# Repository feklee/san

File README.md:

Introduction
============

*Knowing yourself is the beginning of all wisdom* ― Aristotle

SAN (Self Aware Network) is an experiment about the [future of
architecture][1]. The network understands its own topology, a first
step towards being able to dynamically adapt to its environment.

SAN is an intermediate step: [Manifesto][6]

Getting started
===============

 1. Build nodes, edges, and the root node.

 2. Program the root node and the nodes.

 3. If using the USB root node, connect that to your computer, then run the web
    app.
    
    If using the WiFi root node, simply connect to it with a web browser.
    
 4. Build a structure.

There may be [apps][5] built on top of the system.

Acknowledgments
===============

  * [Cong Nguyen][2] for helping with PCB design

  * [David Mickisch][3] for mathematical advise and for writing the
    experimental [San-Optimizer][4]
    
  * Herbert Poetzl for advice on electronics and for the suggestion to
    use optical communication between nodes
  
  * Loay Yari for helping with PCB design and manufacturing
    
  * [Pietro Mincuzzi][7] for the o-ring trick
  
  * Kliment for advice on electronics, optics, and the ESP32

License
=======

Except where noted otherwise, files are licensed under the WTFPL.

Copyright © 2018–2020 [Felix E. Klee](felix.klee@inka.de)

This work is free. You can redistribute it and/or modify it under the terms of
the Do What The Fuck You Want To Public License, Version 2, as published by Sam
Hocevar. See the COPYING file for more details.

[1]: https://feklee.github.io/san/notes/128a47a0-23ea-11e9-a8da-000c296198cf/
[2]: https://github.com/rampadc
[3]: https://github.com/davidblitz
[4]: https://github.com/davidblitz/san-optimizer
[5]: https://feklee.github.io/san/notes/f8d89da9-c285-4b5a-921b-7af3444b9229/
[6]: https://feklee.github.io/san/notes/0411b82f-268f-46b2-9563-efaf14a68a41/
[7]: https://pietro.mincuzzi.asia

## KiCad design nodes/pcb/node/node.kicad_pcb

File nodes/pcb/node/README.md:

This repo has been merged into the [SAN][1] repo as a [Git subtree][2].

To update this repo from within the SAN repo, [run][3] from the toplevel of the
SAN working tree:

    git subtree push --prefix=$PATH_OF_TREE $THIS_REPO master

Replace `$PATH_OF_TREE` and `$THIS_REPO` appropriately.

[1]: https://github.com/feklee/san
[2]: https://git-scm.com/book/en/v1/Git-Tools-Subtree-Merging
[3]: https://stackoverflow.com/a/55400804/282729

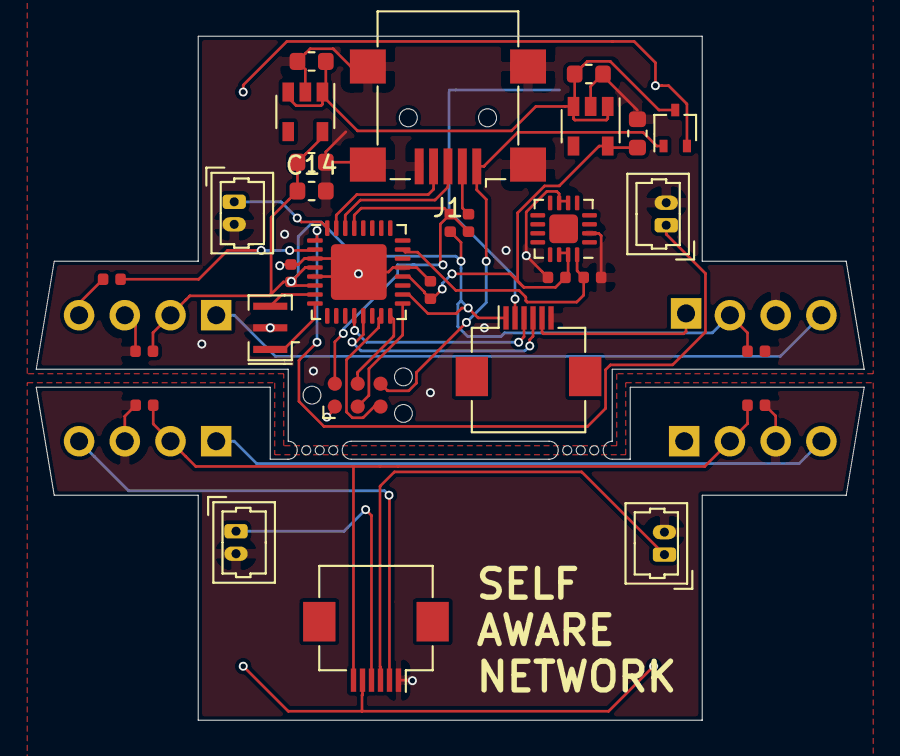
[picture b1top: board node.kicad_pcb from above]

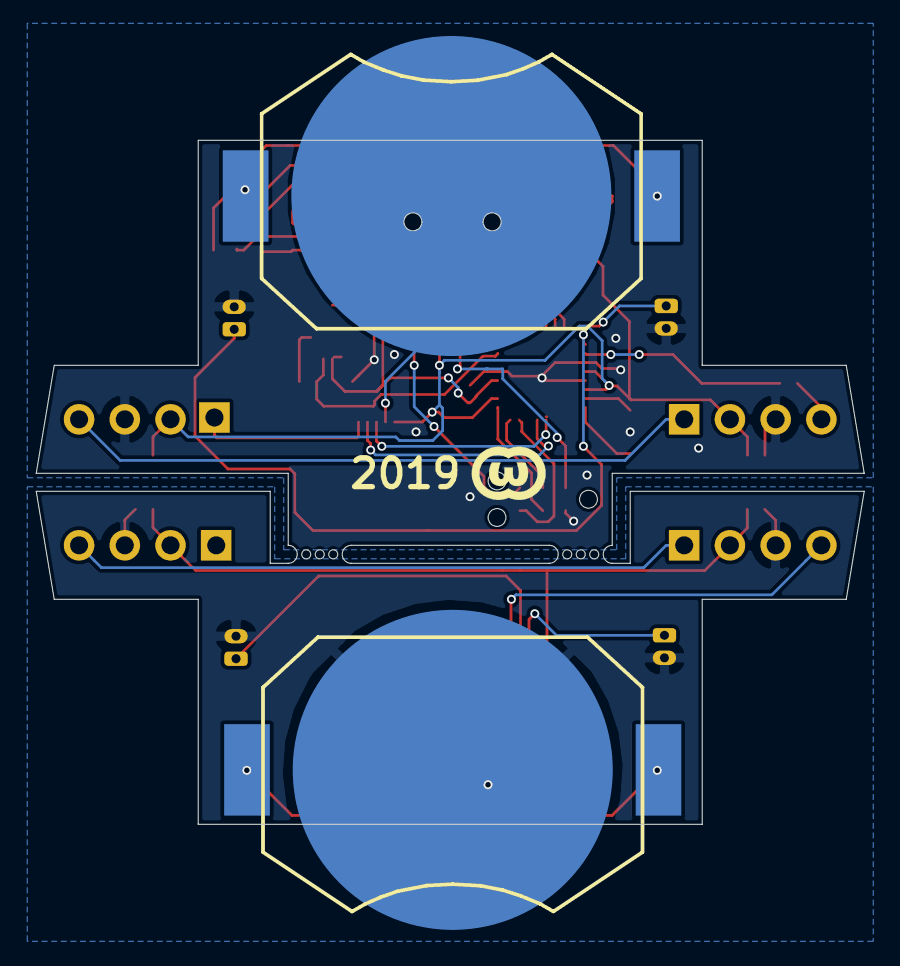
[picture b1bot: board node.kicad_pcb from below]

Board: 2 copper layers, 46.0 x 38.0 mm, 38 parts (2 on the bottom side), 32 nets.

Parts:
BT1, BT2: CR2032; BK-912
C1, C2, C3, C4, C14: 1u; C_0603_1608Metric
C5, C6, C7, C8, C9, C10, C11, C12, C13: 0.1u; C_0402_1005Metric
D1: BAT54CW; SOT-323_SC-70
D2, D3, D4, D5: WS2812D-F5
J1: USB_B_Mini; USB_Mini-B
J2: TC2030_NL; Tag-Connect_TC2030-IDC-NL_2x03_P1.27mm_Vertical
J3, J6: FFC-0.5MM-6POS; Hirose_FH12-6S-0.5SH_1x06-1MP_P0.50mm_Horizontal
J4: Port_1; Molex_PicoBlade_53047-0210_1x02_P1.25mm_Vertical
J5: Port_2; Molex_PicoBlade_53047-0210_1x02_P1.25mm_Vertical
J7: Port_3; Molex_PicoBlade_53047-0210_1x02_P1.25mm_Vertical
J8: Port_4; Molex_PicoBlade_53047-0210_1x02_P1.25mm_Vertical
R1: 10K; R_0402_1005Metric
R2: 470R; R_0402_1005Metric
U1: PMIC-LDO-XC6204B332MR_SOT23-5; SOT-23-5
U2: LP2985-5.0; SOT-23-5
U3: ATmega328P-MU; QFN-32-1EP_5x5mm_P0.5mm_EP3.1x3.1mm
U4: ADXL337; LFCSP-16-1EP_3x3mm_P0.5mm_EP1.6x1.6mm
Y1: 16MHz; Resonator_SMD_muRata_CSTxExxV-3Pin_3.0x1.1mm
mouse-bite: VAL**; mouse-bite
mouse-bite#2: VAL**; mouse-bite

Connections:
+3V3: C4.1, C5.1, C8.1, U1.5, U3.20, U4.14, U4.15
+5V: C3.2, C6.1, C9.1, C11.1, C14.1, D2.2, D3.2, J3.1, R1.1, U2.5, U3.4, U3.6, U3.18
+5VB: C12.1, C13.1, D4.2, D5.2, J6.6
/Bottom hemisphere/BATT-BOT: BT2.1, J6.5
/Bottom hemisphere/BNC-3: J6.4, J7.1
/Bottom hemisphere/BNC-4: J6.3, J8.1
/Bottom hemisphere/DOUT: D4.4, J6.2
/Top Hemisphere/+5V_EXT: D1.1, J1.1, J2.6
/Top Hemisphere/BATT: BT1.1, D1.2
/Top Hemisphere/BATT-BOT: BT1.2, J3.2
/Top Hemisphere/BNC-1: J4.1, U3.32
/Top Hemisphere/BNC-2: J5.1, U3.1
/Top Hemisphere/BNC-3: J3.3, U3.12
/Top Hemisphere/BNC-4: J3.4, U3.13
/Top Hemisphere/DIN-TOP: D2.4, R2.1
/Top Hemisphere/DOUT: D3.1, J3.5
/Top Hemisphere/DTR: C7.1, J1.2
/Top Hemisphere/MISO: J2.4, U3.16
/Top Hemisphere/MOSI: J2.5, U3.15
/Top Hemisphere/RXI: J1.3, U3.30
/Top Hemisphere/SCK: J2.3, U3.17
/Top Hemisphere/TXO: J1.4, U3.31
/Top Hemisphere/VIN: C1.1, C2.1, D1.3, U1.1, U1.3, U2.1, U2.3
/Top Hemisphere/Z-ACCEL: C10.1, U3.23, U4.16
/Top Hemisphere/~RST: C7.2, J2.2, R1.2, U3.29
GND: C1.2, C2.2, C3.1, C4.2, C5.2, C6.2, C8.2, C9.2, C10.2, C11.2, C14.2, D2.3, D3.3, J1.5, J1.6, J2.1, J3.6, J4.2, J5.2, U1.2, U2.2, U3.3, U3.5, U3.21, U3.33, U4.2, U4.6, U4.7, Y1.2
GNDB: BT2.2, C12.2, C13.2, D4.3, D5.3, J6.1, J7.2, J8.2
unnamed: D2.1, D3.4
unnamed: D4.1, D5.4
unnamed: R2.2, U3.2
unnamed: U3.7, Y1.3
unnamed: U3.8, Y1.1

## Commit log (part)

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2019-06-13 Mention mood
2019-06-13 Add app ideas
2019-06-13 Allow offsetting curve out of the way
2019-06-13 Turn cursor to pointer over buttons
2019-06-15 Prevent accidental overscroll
2019-06-15 Change spectrum analyzer stroke
2019-06-15 Make sawtooth button label graphical
2019-06-15 Switch from line elements to more compact path el.
2019-06-15 Create random pattern for white noise
2019-06-15 Show noise when selected
2019-06-15 Share noise source creation function
2019-06-16 Filter noise
2019-06-16 Increase maximum frequency
2019-06-16 Increase maximum detuning to full octave
2019-06-20 Add idea for machine learning based self awareness
2019-06-20 Center show button
2019-06-20 Set input gains once per module (fixes issues)
2019-06-20 Source -> Generator (to avoid confusion)
2019-06-20 Simplify setting detuning
2019-06-20 Make JSLint happy
2019-06-20 Mention hack
2019-06-20 Remove unneeded variable
2019-06-21 Let body know when audio is muted
2019-06-21 Hide analyzer when muted
2019-06-21 Reduce resolution of graphical analyzer
2019-07-07 Point to molecular conformation
2019-07-07 Quote Aristotle
2019-07-07 Reword
2019-07-10 Add master plan
2019-07-10 Make shorter
2019-07-10 Separate role of SAN in own section
2019-07-10 Update styling
2019-07-12 Add ideas outside of SAN
2019-07-13 Mention mushrooms
2019-07-19 Improve readability of what happens in generator
2019-07-19 Clarify position of amplitude in generator chain
2019-07-19 Clarify position of filters 2 and 3
2019-07-19 Put everything output related into one object
2019-07-19 Everywhere: generator type -> generator source type
2019-07-20 It’s a manifesto!
2019-07-20 Add heading
2019-07-22 Add cutoff filter
2019-07-23 Send audio module updates while operating controls
2019-07-23 Enter idea for text entry
2019-07-23 Remove unused settings
2019-07-23 Add functionality to restart web socket connection
2019-07-23 Switch to new web socket interface
2019-07-23 Fix: Initial cutoff frequency too low
2019-09-05 Make settings global
2019-09-05 Add documentation for WiFi root node
2019-09-05 Move all hardware into a dedicated directory
2019-09-23 Emphasize criteria
2019-10-03 Mention that it’s for desktop system
2019-10-04 Illustrate IR transceiver
2019-10-05 Add light pipe
2019-10-05 Detail possibilities for MCU and CPU
2019-10-05 Mention board with accelerometer on board
2019-10-05 Output
2019-10-07 Illustrate with images how to burn boot loader
2019-10-07 Fix: sketch name struck out
2019-10-07 Add info about power bank
2019-10-12 Update path to shared settings
2019-10-12 Fix: Shared settings cannot be loaded
2019-10-13 Use null for no cutoff
2019-10-14 Simplify enabling/disabling filters
2019-10-14 Remove apparently outdated comment
2019-10-15 Try including X3D
2019-10-15 Simplify naming
2019-10-16 Add example power bank product
2019-10-16 Mention alternative for mounting power bank
2019-10-16 Add node 3D model
2019-10-17 Reduce page width for readability
2019-10-17 Play with alternative fitness
2019-10-20 Add hole positions
2019-10-20 Save
2019-10-21 Detail production process and cost
2019-10-21 Add custom IDs
2019-10-24 Add detailed edge connector dimensions
2019-10-24 Mention that light pipe is not necessarily needed
2019-10-24 Fix: wrong distance
2019-11-02 Mention that interface is serial
2019-11-02 Add HTTP pair server
2019-11-02 Permanently connect A to root node
2019-11-08 Add firmware (not fully functional)
2019-11-08 Provide basic information
2019-11-08 Assign static IP
2019-11-08 Switch to mode 3, disable clock div
2019-11-08 Make log tags consistent
2019-11-08 Set IP after receiving SPI message
2019-11-08 Update path for shared settings
2019-11-08 Start merging functionality of desktop system
2019-11-14 Make directory name more generic, not only ESP-EYE
2019-11-16 Create panel showing node UI next to structure
2019-11-16 Add video video stream with fallback to noise
2019-11-17 Add schematic of main PCB
2019-11-17 Add schematic of port PCB
2019-11-17 Update BOM
2019-11-17 Add connector, update numbering
2019-11-17 Remove lock file
2019-11-17 Give example how to view serial output
2019-11-21 Update WiFi network
2019-11-21 Update components
2019-11-21 Move b/w filter from camera to CSS
2019-11-25 Create and document upload script
2019-11-25 Fix: wrong IP range for video stream
2019-11-28 Allow specification of MHz
2019-11-28 Fix: Pair not sent by SPI
2019-12-02 Add colors for W-Z
2019-12-03 Make naming great again
2019-12-04 Change (disabled) test code
2019-12-20 Allow simulating always connected node A
2020-01-06 Give credit
2020-01-06 Prepare for merging with master
2020-01-06 Undo rename
2020-01-07 Use newer serial module (old one doesn’t compile)
2020-01-07 Reinstall
2020-01-10 Make Powell iterator take fitness of correct sign
2020-01-10 Enforce naming conventions
2020-01-10 Use Powell’s method from separate repo
2020-01-13 Fix: serial port list doesn’t work
2020-01-17 Remove bad character
2020-01-20 Add Rhino Grasshopper component
2020-01-20 Broadcast graph
2020-01-20 Bump node version
2020-01-20 Output colors of nodes
2020-01-20 Simplify field names
2020-01-20 Clean up
2020-01-20 Fix description
2020-01-20 Add option for center point, and randomly rotate
2020-01-21 Don’t log graph
2020-01-21 Factor out publication of graph
2020-01-21 Say what it’s about
2020-01-21 Include axes in graph
2020-01-21 Fix: Debug code misses module
2020-01-26 Make URL configurable
2020-01-26 Change default WebSocket
2020-01-26 Clean up parameters
2020-01-26 Update description
2020-01-31 Orient node along its axis
2020-02-05 Send data during SPI transmission (for test)
2020-02-05 Tweak
2020-02-07 Factor out SPI transfer
2020-02-07 Experiment
2020-02-10 Reformat
2020-02-10 Switch from SPI mode 3 to mode 1
2020-02-11 Make setting of LEDs work, and refactor
2020-02-11 Update format of compressed colors
2020-02-11 Add troubleshooting
2020-02-12 Change GW IP (IP conflict at Dim Sum Labs)
2020-02-12 Add command interface
2020-02-12 Add interface to send data via SPI
2020-02-14 Point out necessity to select camera
2020-02-14 Simplify URLs
2020-02-14 Remove debugging printing
2020-02-15 Remove debug output
2020-02-15 Make shared settings compile with C
2020-02-15 Handle #define expressions
2020-02-15 Point out fragility
2020-02-15 Fix typo
2020-02-15 Use shared gateway in frontend
2020-02-17 Extract WiFi gateway
2020-02-17 Implement color command
2020-02-17 Add timestamp to log
2020-02-17 Encapsulate time stamp
2020-02-17 Factor out elapsed time
2020-02-17 Implement rebroadcasting
2020-02-17 Inject connection type
2020-02-17 Remove wifi gateway extraction
2020-02-17 Detail description
2020-02-17 Fix: Callback not executed
2020-02-17 Remove unnecessary state variable
2020-02-17 Circumvent parser bug: node A colors not correct
2020-02-18 Add TriState for testing; Add connection
2020-02-18 Add component to get node point
2020-02-18 Introduce utility function to get index of node
2020-02-18 Add color inputs
2020-02-18 Fix: missing components
2020-02-18 Move node IP calculation to utility function
2020-02-18 Allow specification of connection type
2020-02-18 Send colors to node only for WiFi connection
2020-02-18 Construct URL from node IP
2020-02-18 Send / Interpret edges as pairs of node IDs
2020-02-18 Just ignore all HTTP exceptions
2020-02-18 Removed tri state parameters for testing
2020-02-18 Introduce command to show edges
2020-02-18 Clean up component that connects to the SAN server
2020-02-18 Fix: wrong log function used
2020-02-19 Add neighbors component
2020-02-19 Introduce new object to store node colors
2020-02-19 Broadcast node colors changes
2020-02-19 Use conic gradient (preparation for 4 node colors)
2020-02-19 Allow four colors on sphere
2020-02-19 Switch to four colors per node
2020-02-19 Refactor handling of colors, read color messages
2020-02-19 Fix circular dependency
2020-02-19 Fix missing module dependency
2020-02-19 Keep colors fresh
2020-02-20 Only send if WebSocket is connected
2020-02-20 Make wires to connection hidden by default
2020-02-20 Only send color update if color has changed
2020-02-20 Update node by WiFi on color change
2020-02-20 Store connection type in module
2020-02-24 Move shared settings to root directory
2020-02-24 Remove option to set clock speed
2020-02-24 Don’t continue on error
2020-02-24 Remove debug messages
2020-02-25 Make compatible with new shared settings
2020-02-25 Max out brightness
2020-02-25 Dial back brightness (drains batteries too fast)
2020-02-25 Update lock file
2020-02-26 Remove debug info
2020-02-26 Fix: doesn’t compile
2020-02-26 Update server IP
2020-02-27 Adapt to new interface of startWebServer
2020-02-28 Throttle ID send period (not sure if necessary)
2020-03-01 Reduce size of features
2020-03-14 Bump acorn from 7.1.0 to 7.1.1 in /webapp
    Bumps [acorn](https://github.com/acornjs/acorn) from 7.1.0 to 7.1.1.
    - [Release notes](https://github.com/acornjs/acorn/releases)
    - [Commits](https://github.com/acornjs/acorn/compare/7.1.0...7.1.1)
2020-08-01 Bump elliptic from 6.5.2 to 6.5.3 in /webapp
    Bumps [elliptic](https://github.com/indutny/elliptic) from 6.5.2 to 6.5.3.
    - [Release notes](https://github.com/indutny/elliptic/releases)
    - [Commits](https://github.com/indutny/elliptic/compare/v6.5.2...v6.5.3)
2020-10-16 Bump npm-user-validate from 1.0.0 to 1.0.1 in /webapp
    Bumps [npm-user-validate](https://github.com/npm/npm-user-validate) from 1.0.0 to 1.0.1.
    - [Release notes](https://github.com/npm/npm-user-validate/releases)
    - [Commits](https://github.com/npm/npm-user-validate/compare/v1.0.0...v1.0.1)
2021-02-05 Include final board designs by Loay
2021-03-10 Bump elliptic from 6.5.2 to 6.5.4 in /webapp
    Bumps [elliptic](https://github.com/indutny/elliptic) from 6.5.2 to 6.5.4.
    - [Release notes](https://github.com/indutny/elliptic/releases)
    - [Commits](https://github.com/indutny/elliptic/compare/v6.5.2...v6.5.4)
2021-03-31 Bump y18n from 3.2.1 to 3.2.2 in /webapp
    Bumps [y18n](https://github.com/yargs/y18n) from 3.2.1 to 3.2.2.
    - [Release notes](https://github.com/yargs/y18n/releases)
    - [Changelog](https://github.com/yargs/y18n/blob/master/CHANGELOG.md)
    - [Commits](https://github.com/yargs/y18n/commits)
2021-08-11 Bump path-parse from 1.0.6 to 1.0.7 in /webapp
    Bumps [path-parse](https://github.com/jbgutierrez/path-parse) from 1.0.6 to 1.0.7.
    - [Release notes](https://github.com/jbgutierrez/path-parse/releases)
    - [Commits](https://github.com/jbgutierrez/path-parse/commits/v1.0.7)
    ---
    updated-dependencies:
    - dependency-name: path-parse
2022-01-27 Bump three from 0.91.0 to 0.137.0 in /webapp
    Bumps [three](https://github.com/mrdoob/three.js) from 0.91.0 to 0.137.0.
    - [Release notes](https://github.com/mrdoob/three.js/releases)
    - [Commits](https://github.com/mrdoob/three.js/commits)
    ---
    updated-dependencies:
    - dependency-name: three
2022-02-12 Bump ajv from 6.10.2 to 6.12.6 in /webapp
    Bumps [ajv](https://github.com/ajv-validator/ajv) from 6.10.2 to 6.12.6.
    - [Release notes](https://github.com/ajv-validator/ajv/releases)
    - [Commits](https://github.com/ajv-validator/ajv/compare/v6.10.2...v6.12.6)
    ---
    updated-dependencies:
    - dependency-name: ajv
2022-06-22 Bump Newtonsoft.Json from 12.0.3 to 13.0.1 in /grasshopper/SAN
    Bumps [Newtonsoft.Json](https://github.com/JamesNK/Newtonsoft.Json) from 12.0.3 to 13.0.1.
    - [Release notes](https://github.com/JamesNK/Newtonsoft.Json/releases)
    - [Commits](https://github.com/JamesNK/Newtonsoft.Json/compare/12.0.3...13.0.1)
    ---
    updated-dependencies:
    - dependency-name: Newtonsoft.Json
2022-12-08 Bump Newtonsoft.Json from 12.0.3 to 13.0.2 in /grasshopper/SAN
    Bumps [Newtonsoft.Json](https://github.com/JamesNK/Newtonsoft.Json) from 12.0.3 to 13.0.2.
    - [Release notes](https://github.com/JamesNK/Newtonsoft.Json/releases)
    - [Commits](https://github.com/JamesNK/Newtonsoft.Json/compare/12.0.3...13.0.2)
    ---
    updated-dependencies:
    - dependency-name: Newtonsoft.Json
